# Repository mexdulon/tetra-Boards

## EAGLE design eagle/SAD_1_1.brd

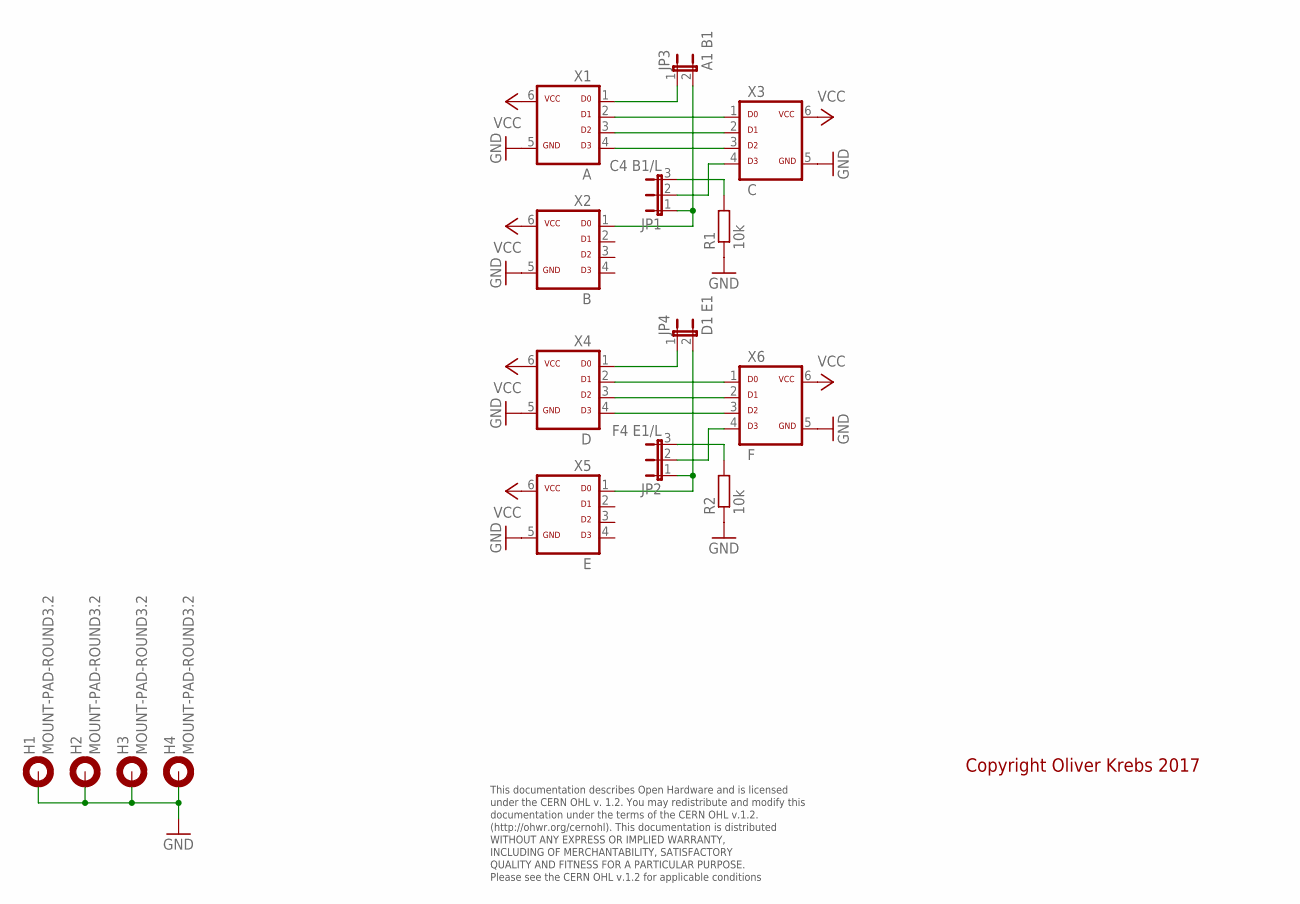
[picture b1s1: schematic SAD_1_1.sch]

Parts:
H1, H2, H3, H4: MOUNT-PAD-ROUND3.2; 3,2-PAD
JP1: C4 B1/L; JP2
JP2: F4 E1/L; JP2
JP3: A1 B1; JP1
JP4: D1 E1; JP1
R1, R2: 10k; 0207/10
X1: A; ML-6
X2: B; ML-6
X3: C; ML-6
X4: D; ML-6
X5: E; ML-6
X6: F; ML-6

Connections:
GND: H1.B3,2, H2.B3,2, H3.B3,2, H4.B3,2, R1.1, R2.1, X1.5, X2.5, X3.5, X4.5, X5.5, X6.5
unnamed: X1.2, X3.1
unnamed: X1.3, X3.2
unnamed: X1.4, X3.3
unnamed: JP1.2, X3.4
unnamed: JP1.1, JP3.2, X2.1
unnamed: JP4.1, X4.1
unnamed: JP3.1, X1.1
unnamed: JP1.3, R1.2
unnamed: JP2.3, R2.2
unnamed: X4.2, X6.1
unnamed: X4.3, X6.2
unnamed: X4.4, X6.3
unnamed: JP2.2, X6.4
unnamed: JP2.1, JP4.2, X5.1
VCC: X1.6, X2.6, X3.6, X4.6, X5.6, X6.6

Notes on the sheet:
This documentation describes Open Hardware and is licensed under the CERN OHL v. 1.2. You may redistribute and modify this documentation under the terms of the CERN OHL v.1.2. (http://ohwr.org/cernohl). This documentation is distributed WITHOUT ANY EXPRESS OR IMPLIED WARRANTY, INCLUDING OF MERCHANT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
Copyright Oliver Krebs 2017

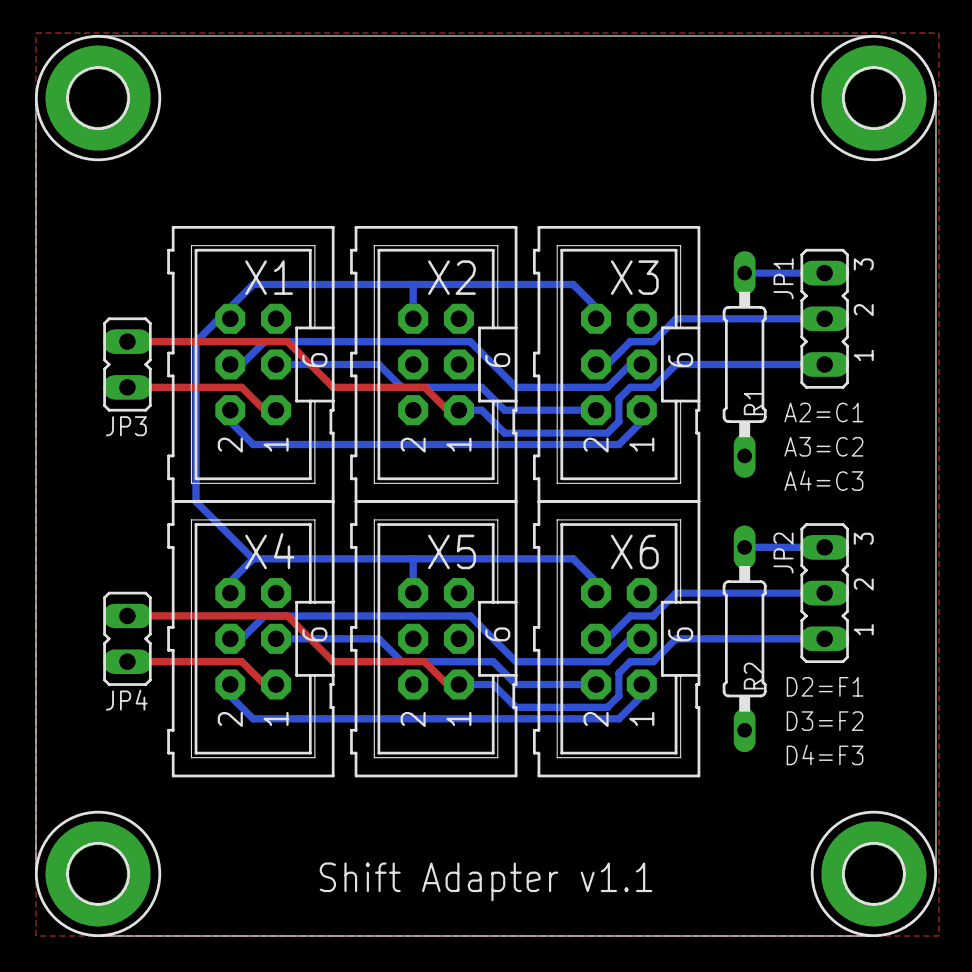
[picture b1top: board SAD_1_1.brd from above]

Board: 2 copper layers, 50.0 x 50.0 mm, 16 parts (0 on the bottom side), 16 nets.

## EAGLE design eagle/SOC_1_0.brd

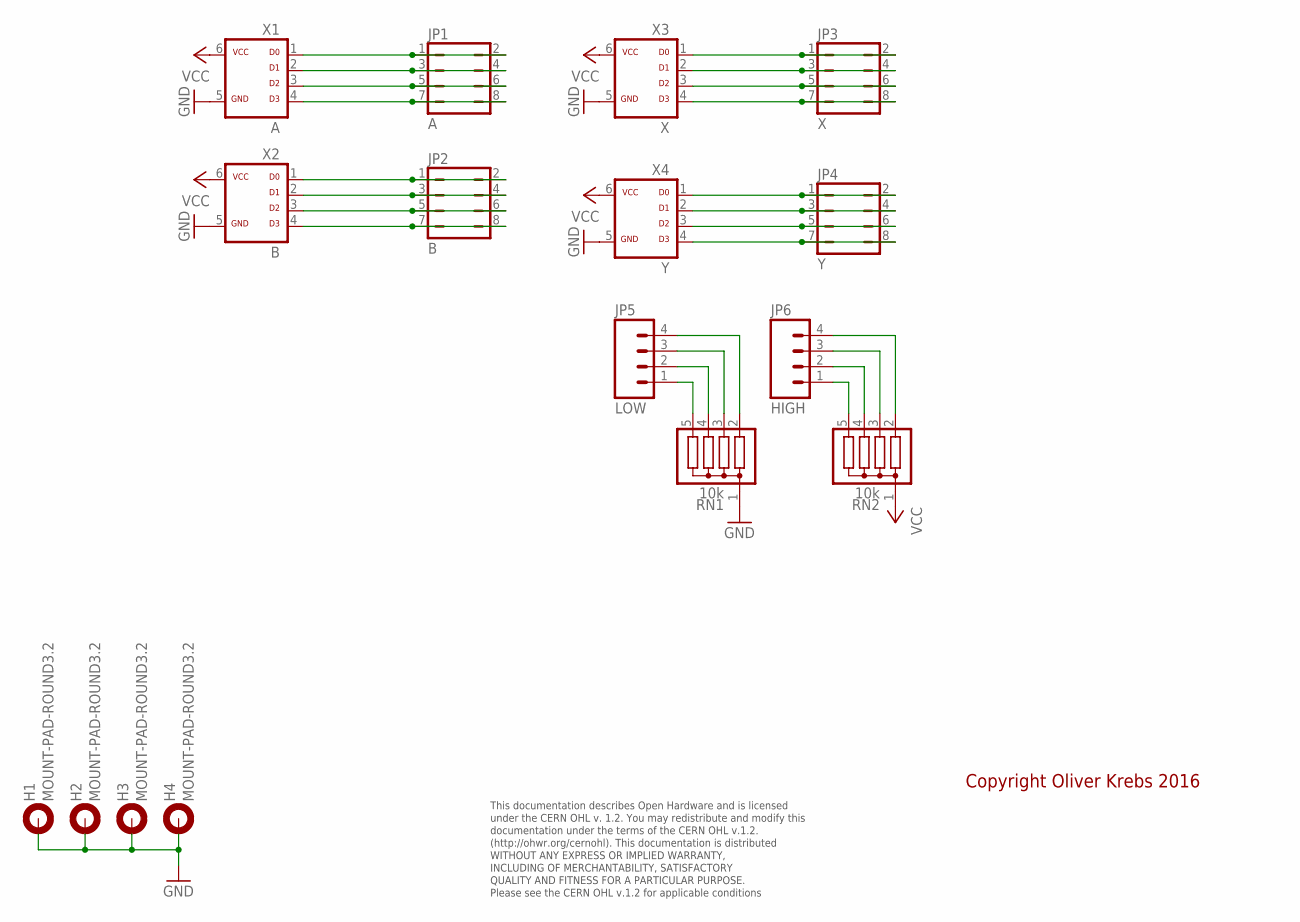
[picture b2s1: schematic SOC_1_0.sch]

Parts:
H1, H2, H3, H4: MOUNT-PAD-ROUND3.2; 3,2-PAD
JP1: A; JP4Q
JP2: B; JP4Q
JP3: X; JP4Q
JP4: Y; JP4Q
JP5: LOW; 1X04
JP6: HIGH; 1X04
RN1, RN2: 10k; SIL5
X1: A; ML-6
X2: B; ML-6
X3: X; ML-6
X4: Y; ML-6

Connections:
GND: H1.B3,2, H2.B3,2, H3.B3,2, H4.B3,2, RN1.1, X1.5, X2.5, X3.5, X4.5
unnamed: JP2.1, JP2.2, X2.1
unnamed: JP2.3, JP2.4, X2.2
unnamed: JP2.5, JP2.6, X2.3
unnamed: JP2.7, JP2.8, X2.4
unnamed: JP4.1, JP4.2, X4.1
unnamed: JP4.3, JP4.4, X4.2
unnamed: JP4.5, JP4.6, X4.3
unnamed: JP4.7, JP4.8, X4.4
unnamed: JP1.1, JP1.2, X1.1
unnamed: JP1.3, JP1.4, X1.2
unnamed: JP1.5, JP1.6, X1.3
unnamed: JP1.7, JP1.8, X1.4
unnamed: JP3.1, JP3.2, X3.1
unnamed: JP3.3, JP3.4, X3.2
unnamed: JP3.5, JP3.6, X3.3
unnamed: JP3.7, JP3.8, X3.4
unnamed: JP5.2, RN1.4
unnamed: JP5.3, RN1.3
unnamed: JP5.1, RN1.5
unnamed: JP5.4, RN1.2
unnamed: JP6.1, RN2.5
unnamed: JP6.2, RN2.4
unnamed: JP6.3, RN2.3
unnamed: JP6.4, RN2.2
VCC: RN2.1, X1.6, X2.6, X3.6, X4.6

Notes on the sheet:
This documentation describes Open Hardware and is licensed under the CERN OHL v. 1.2. You may redistribute and modify this documentation under the terms of the CERN OHL v.1.2. (http://ohwr.org/cernohl). This documentation is distributed WITHOUT ANY EXPRESS OR IMPLIED WARRANTY, INCLUDING OF MERCHANT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
Copyright Oliver Krebs 2016

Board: 2 copper layers, 16 parts (0 on the bottom side), 26 nets, no tracks yet.

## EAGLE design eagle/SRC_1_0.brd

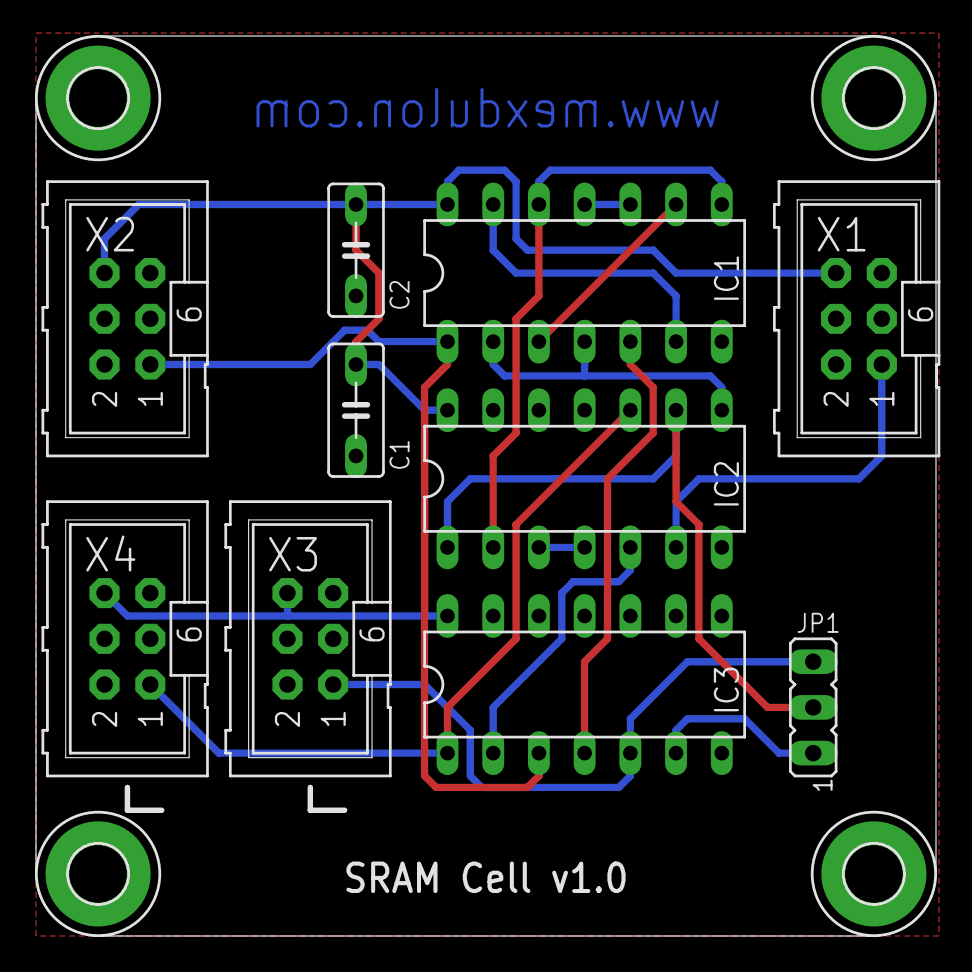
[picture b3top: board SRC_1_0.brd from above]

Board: 2 copper layers, 50.0 x 50.0 mm, 14 parts (0 on the bottom side), 16 nets.

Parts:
C1, C2: 100n; C050-030X075
H1, H2, H3, H4: MOUNT-PAD-ROUND3.2; 3,2-PAD
IC1: 74HC00N; DIL14
IC2: 74HC08N; DIL14
IC3: 74HC04N; DIL14
JP1: Sel n/p; JP2-U
X1: Out; ML-6
X2: In Data; ML-6
X3: Select; ML-6
X4: Write; ML-6

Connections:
GND: C1.2, C2.2, H1.B3,2, H2.B3,2, H3.B3,2, H4.B3,2, IC1.7, IC2.7, IC2.12, IC2.13, IC3.7, IC3.9, IC3.11, IC3.13, X1.5, X2.5, X3.5, X4.5
unnamed: IC2.3, IC2.4
unnamed: IC1.2, IC1.4, IC2.8
unnamed: IC1.1, IC3.3, X2.1
unnamed: IC2.1, IC2.9, JP1.2
unnamed: IC2.10, IC3.1, X4.1
unnamed: IC1.3, IC1.9
unnamed: IC1.6, IC1.13
unnamed: IC1.8, IC1.12, IC2.2
unnamed: IC1.5, IC3.4
unnamed: IC1.10, IC1.11
unnamed: IC2.6, X1.1
unnamed: IC2.5, IC3.2
unnamed: IC3.6, JP1.1
unnamed: IC3.5, JP1.3, X3.1
VCC: C1.1, C2.1, IC1.14, IC2.14, IC3.14, X1.6, X2.6, X3.6, X4.6

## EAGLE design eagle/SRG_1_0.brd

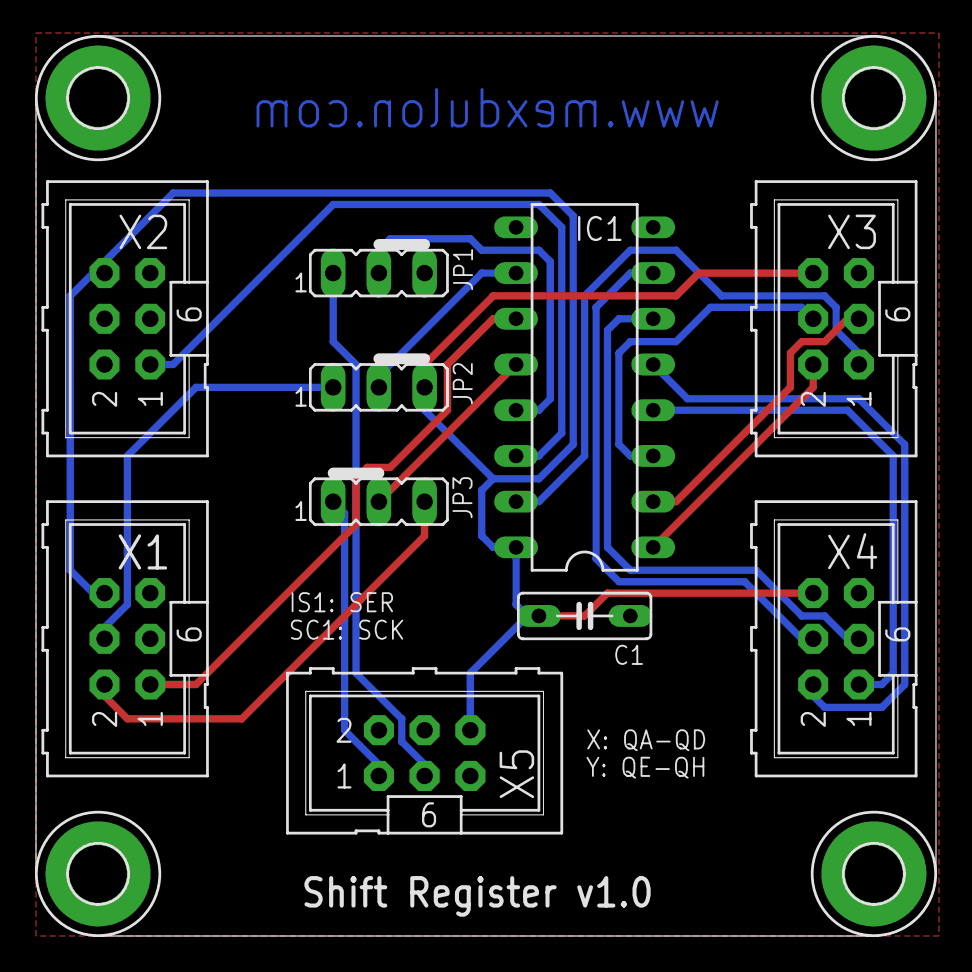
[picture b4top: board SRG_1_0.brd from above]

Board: 2 copper layers, 50.0 x 50.0 mm, 14 parts (0 on the bottom side), 19 nets.

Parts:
C1: 100n; C050-025X075
H1, H2, H3, H4: MOUNT-PAD-ROUND3.2; 3,2-PAD
IC1: 74HC595N; DIL16
JP1: /G RC3/L; JP2-U
JP2: /SCL SC4/H; JP2-U
JP3: RCK RC1/SC2; JP2-U
X1: Serial Ctrl; ML-6
X2: In Serial; ML-6
X3: Out X; ML-6
X4: Out Y; ML-6
X5: Reg Ctrl; ML-6

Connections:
GND: C1.2, H1.B3,2, H2.B3,2, H3.B3,2, H4.B3,2, IC1.8, JP1.3, X1.5, X2.5, X3.5, X4.5, X5.5
unnamed: IC1.15, X3.1
unnamed: IC1.1, X3.2
unnamed: IC1.2, X3.3
unnamed: IC1.3, X3.4
unnamed: IC1.4, X4.1
unnamed: IC1.5, X4.2
unnamed: IC1.6, X4.3
unnamed: IC1.7, X4.4
unnamed: IC1.14, X2.1
unnamed: IC1.10, JP2.2
unnamed: IC1.11, X1.1
unnamed: IC1.12, JP3.2
unnamed: IC1.13, JP1.2
unnamed: JP1.1, X5.3
unnamed: JP2.1, X1.4
unnamed: JP3.1, X5.1
unnamed: JP3.3, X1.2
VCC: C1.1, IC1.16, JP2.3, X1.6, X2.6, X3.6, X4.6, X5.6

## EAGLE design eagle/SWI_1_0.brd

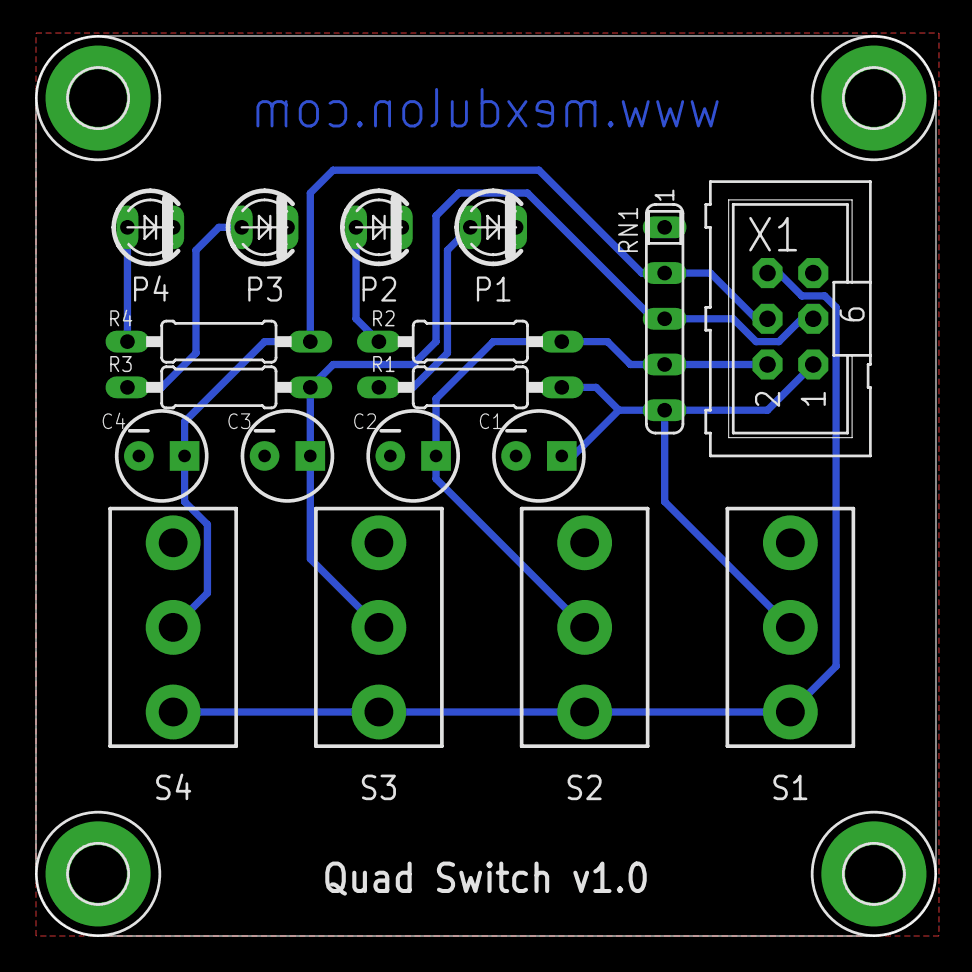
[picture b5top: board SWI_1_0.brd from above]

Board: 2 copper layers, 50.0 x 50.0 mm, 22 parts (0 on the bottom side), 10 nets.

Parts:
C1, C2, C3, C4: 1u; CPOL-RADIAL-10UF-25V
H1, H2, H3, H4: MOUNT-PAD-ROUND3.2; 3,2-PAD
P1, P2, P3, P4: LED3MM
R1, R2, R3, R4: 220; 0207/10
RN1: 10k; SIL5
S1, S2, S3, S4: SWITCH-AS500APC
X1: Out; ML-6

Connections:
GND: C1.2, C2.2, C3.2, C4.2, H1.B3,2, H2.B3,2, H3.B3,2, H4.B3,2, P1.K, P2.K, P3.K, P4.K, RN1.1, X1.5
unnamed: C1.1, R1.1, RN1.5, S1.P, X1.1
unnamed: C2.1, R2.1, RN1.4, S2.P, X1.2
unnamed: C3.1, R3.1, RN1.3, S3.P, X1.3
unnamed: C4.1, R4.1, RN1.2, S4.P, X1.4
unnamed: P1.A, R1.2
unnamed: P2.A, R2.2
unnamed: P3.A, R3.2
unnamed: P4.A, R4.2
VCC: S1.O, S2.O, S3.O, S4.O, X1.6

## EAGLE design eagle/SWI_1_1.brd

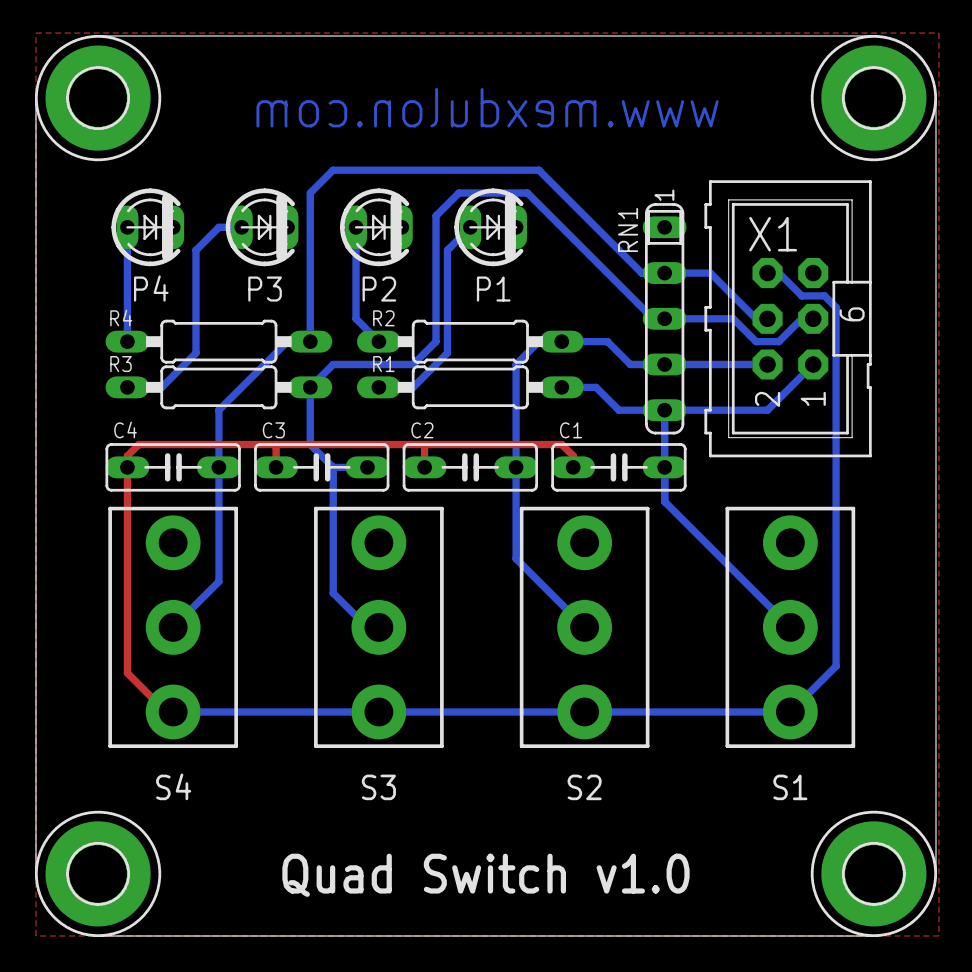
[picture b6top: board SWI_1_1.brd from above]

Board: 2 copper layers, 50.0 x 50.0 mm, 22 parts (0 on the bottom side), 10 nets.

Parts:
C1, C2, C3, C4: 1uF; C050-025X075
H1, H2, H3, H4: MOUNT-PAD-ROUND3.2; 3,2-PAD
P1, P2, P3, P4: LED3MM
R1, R2, R3, R4: 220; 0207/10
RN1: 10k; SIL5
S1, S2, S3, S4: SWITCH-AS500APC
X1: Out; ML-6

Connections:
GND: H1.B3,2, H2.B3,2, H3.B3,2, H4.B3,2, P1.K, P2.K, P3.K, P4.K, RN1.1, X1.5
unnamed: C1.2, R1.1, RN1.5, S1.P, X1.1
unnamed: C2.2, R2.1, RN1.4, S2.P, X1.2
unnamed: C3.2, R3.1, RN1.3, S3.P, X1.3
unnamed: C4.2, R4.1, RN1.2, S4.P, X1.4
unnamed: P1.A, R1.2
unnamed: P2.A, R2.2
unnamed: P3.A, R3.2
unnamed: P4.A, R4.2
VCC: C1.1, C2.1, C3.1, C4.1, S1.O, S2.O, S3.O, S4.O, X1.6

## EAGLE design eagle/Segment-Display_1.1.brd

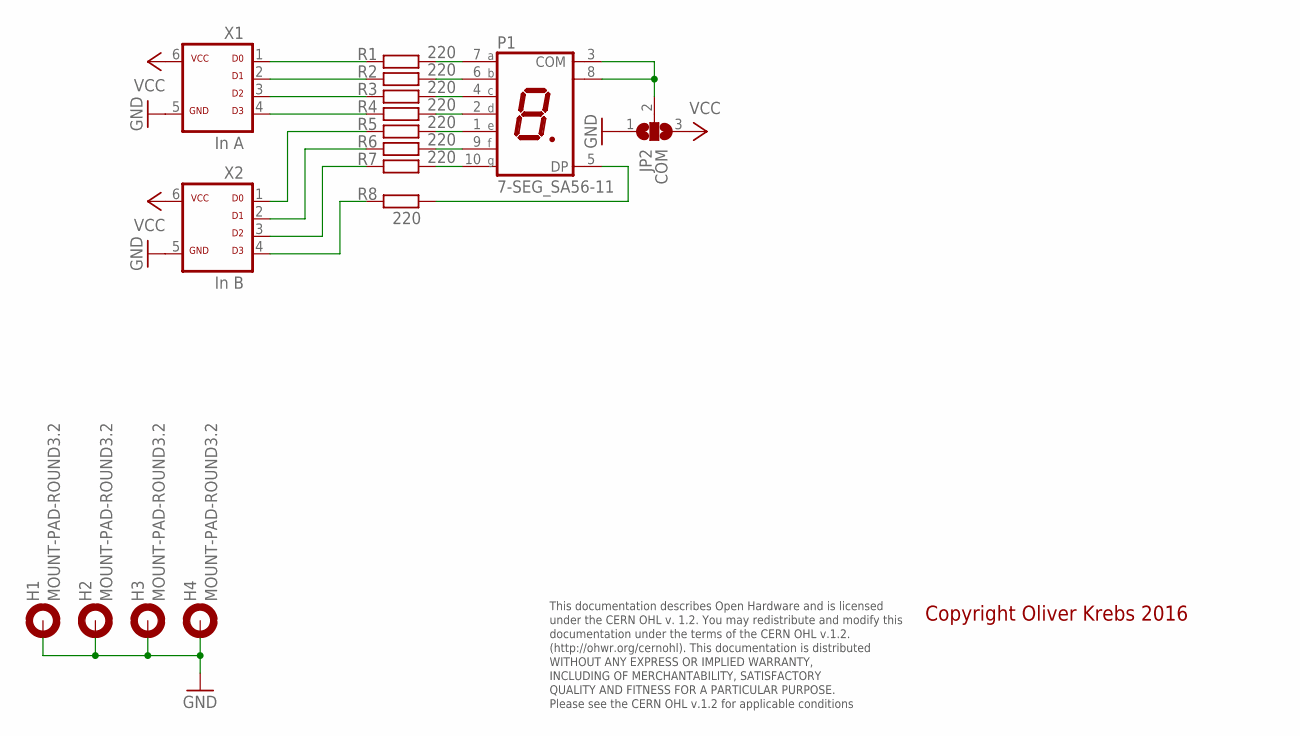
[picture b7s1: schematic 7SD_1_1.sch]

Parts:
H1, H2, H3, H4: MOUNT-PAD-ROUND3.2; 3,2-PAD
JP2: COM; SJ_2
P1: 7-SEG_SA56-11; SA56-11
R1, R2, R3, R4, R5, R6, R7, R8: 220; 0207/10
X1: In A; ML-6
X2: In B; ML-6

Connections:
GND: H1.B3,2, H2.B3,2, H3.B3,2, H4.B3,2, JP2.1, X1.5, X2.5
unnamed: R1.1, X1.1
unnamed: R2.1, X1.2
unnamed: R3.1, X1.3
unnamed: R4.1, X1.4
unnamed: P1.7 (A), R1.2
unnamed: P1.6 (B), R2.2
unnamed: P1.4 (C), R3.2
unnamed: P1.2 (D), R4.2
unnamed: P1.1 (E), R5.2
unnamed: P1.9 (F), R6.2
unnamed: P1.10 (G), R7.2
unnamed: P1.5 (DP), R8.2
unnamed: R5.1, X2.1
unnamed: R6.1, X2.2
unnamed: R7.1, X2.3
unnamed: R8.1, X2.4
unnamed: JP2.2, P1.3 (COM), P1.8 (COM)
VCC: JP2.3, X1.6, X2.6

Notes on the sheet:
This documentation describes Open Hardware and is licensed under the CERN OHL v. 1.2. You may redistribute and modify this documentation under the terms of the CERN OHL v.1.2. (http://ohwr.org/cernohl). This documentation is distributed WITHOUT ANY EXPRESS OR IMPLIED WARRANTY, INCLUDING OF MERCHANT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
Copyright Oliver Krebs 2016

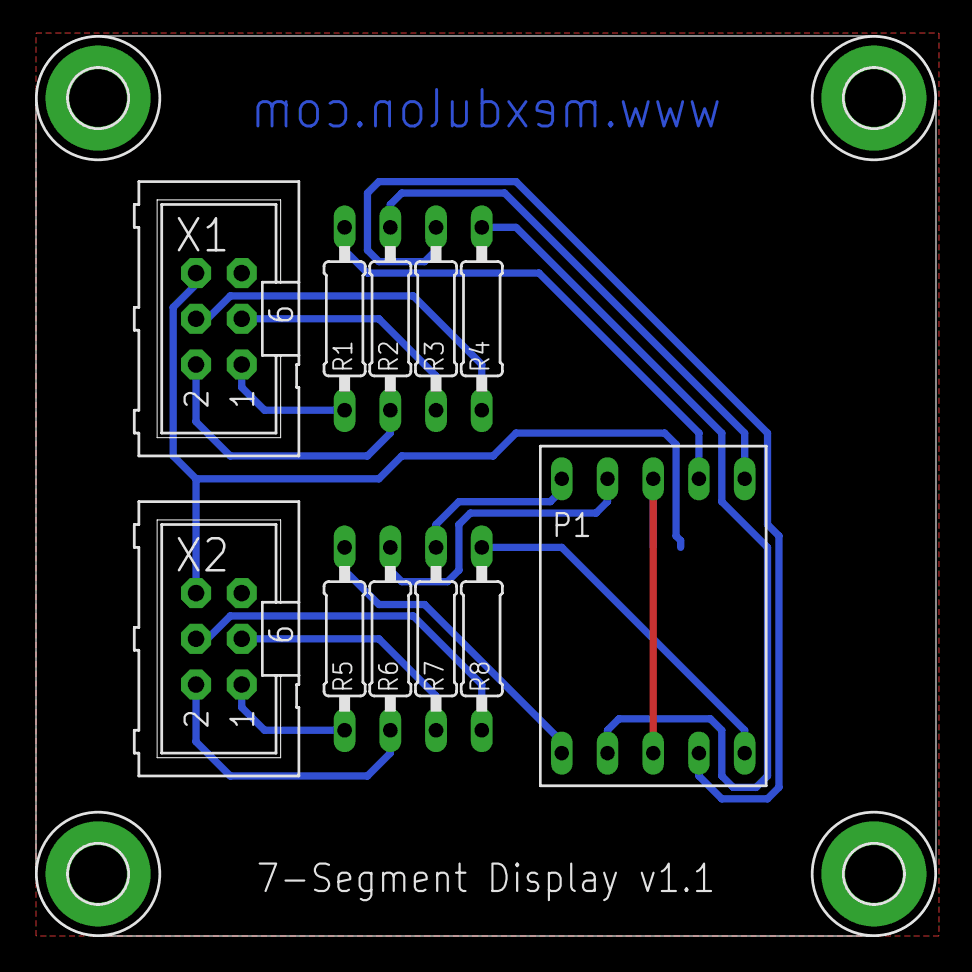
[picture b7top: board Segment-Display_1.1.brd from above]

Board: 2 copper layers, 50.0 x 50.0 mm, 16 parts (1 on the bottom side), 19 nets.

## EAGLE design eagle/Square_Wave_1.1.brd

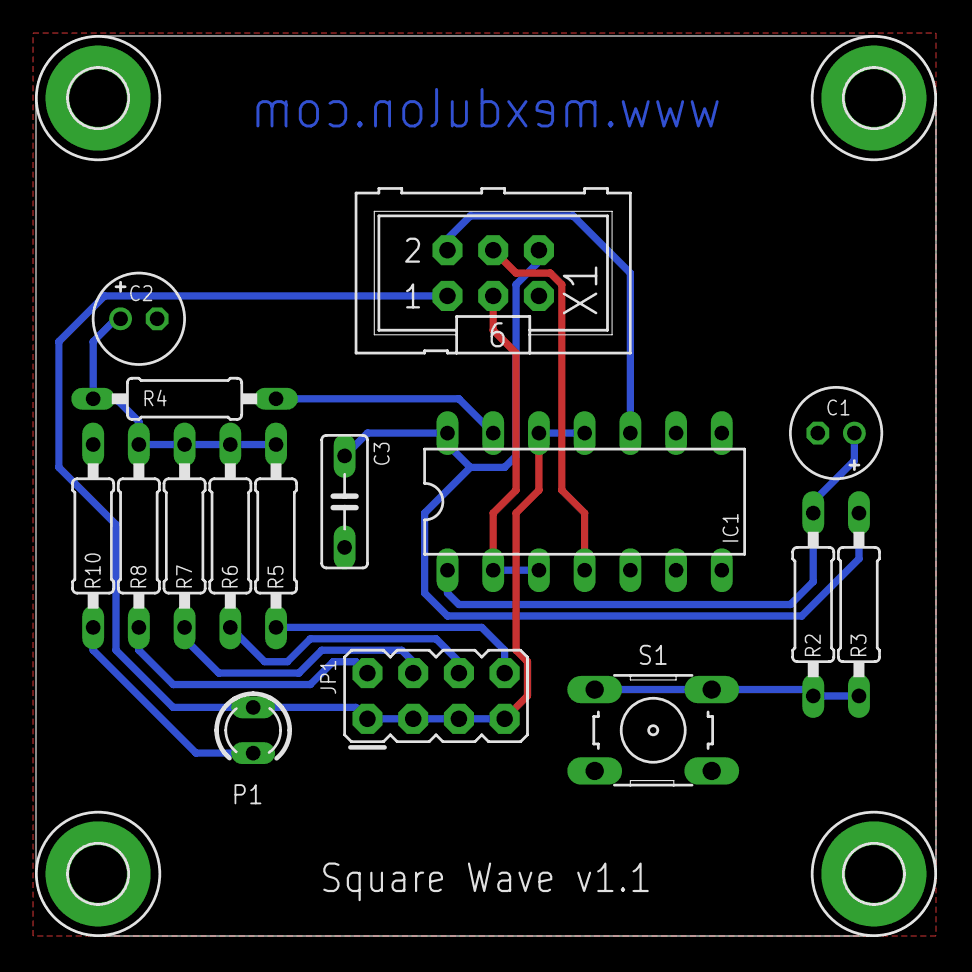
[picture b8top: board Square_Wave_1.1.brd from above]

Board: 2 copper layers, 50.0 x 50.0 mm, 20 parts (0 on the bottom side), 15 nets.

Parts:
C1: 1u; E2-5
C2: 10u; E2-5
C3: 100n; C050-025X075
H1, H2, H3, H4: MOUNT-PAD-ROUND3.2; 3,2-PAD
IC1: 74HC14N; DIL14
JP1: Frequency; JP4Q
P1: LED3MM
R2: 22k; 0207/10
R3, R4, R6: 10k; 0207/10
R5: 100k; 0207/10
R7: 1k; 0207/10
R8: 100R; 0207/10
R10: 220R; 0207/10
S1: Reset; B3F-10XX
X1: Out; ML-6

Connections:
GND: C1.-, C2.-, C3.2, H1.B3,2, H2.B3,2, H3.B3,2, H4.B3,2, IC1.5, IC1.7, IC1.9, R10.1, S1.3, S1.4, X1.5
unnamed: P1.K, R10.2
unnamed: IC1.4, X1.4
unnamed: IC1.2, IC1.3, X1.3
unnamed: IC1.11, IC1.12, JP1.1, JP1.3, JP1.5, JP1.7, P1.A, X1.1
unnamed: JP1.8, R5.2
unnamed: JP1.6, R6.2
unnamed: JP1.4, R7.2
unnamed: JP1.2, R8.2
unnamed: IC1.13, R4.2
unnamed: C2.+, R4.1, R5.1, R6.1, R7.1, R8.1
unnamed: IC1.10, X1.2
unnamed: R2.1, R3.1, S1.1, S1.2
unnamed: C1.+, IC1.1, R2.2
VCC: C3.1, IC1.14, R3.2, X1.6

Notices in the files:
eagle/SOC_1_0.brd:
Licensed under CERN OHL v.1.2
parts and their libraries:
SparkFun-Connectors: Licensing: Creative Commons ShareAlike 4.0 International - https://creativecommons.org/licenses/by-sa/4.0
